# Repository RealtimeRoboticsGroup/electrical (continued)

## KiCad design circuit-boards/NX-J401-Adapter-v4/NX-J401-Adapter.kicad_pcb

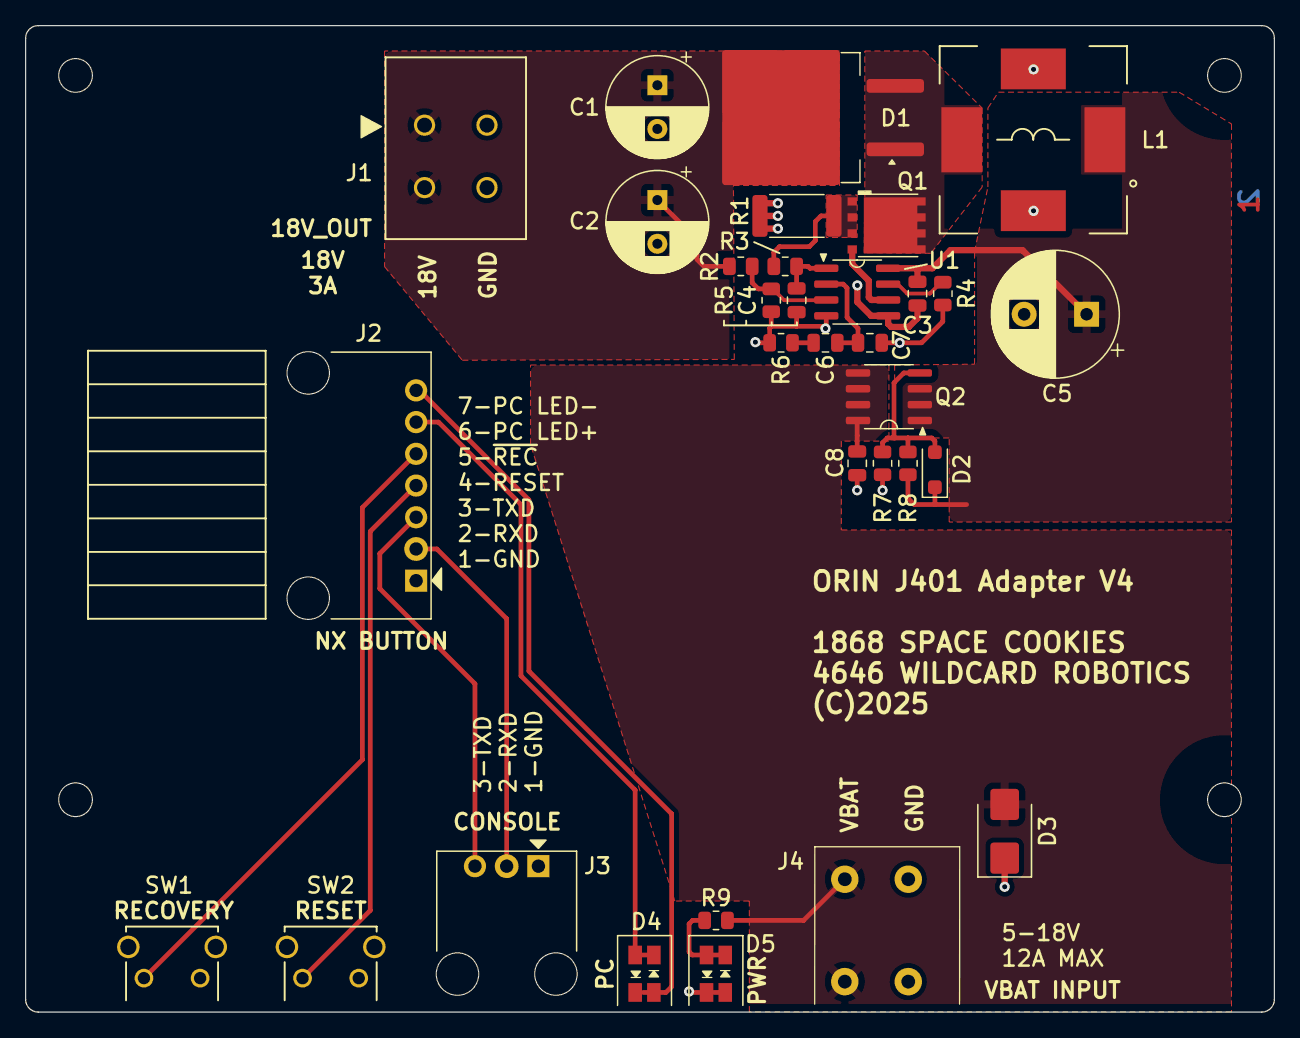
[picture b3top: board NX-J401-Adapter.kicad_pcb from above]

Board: 2 copper layers, 100.0 x 79.0 mm, 36 parts (0 on the bottom side), 21 nets.

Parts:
C1, C2: 82uF 35V; CP_Radial_D8.0mm_P3.50mm
C3, C6: 0.22uF-10%-50V-0805; C_0805_2012Metric
C4: 10pF-5%-50V-0805; C_0805_2012Metric
C5: 330uF 35V; CP_Radial_D10.0mm_P5.00mm
C7: 0.01uF-10%-50V-0805; C_0805_2012Metric
C8: 22uF-20%-25V-0805; C_0805_2012Metric
D1: STPS20M100SG-TR; TO-263-2
D2: 15V; D_SOD-123F
D3: 15V; D_SMB
D4: PC; LED-Dialight-5913001858F
D5: PWR; LED-Dialight-5913001858F
H1, H2, H3, H4: MountingHole; MountingHole_2.7mm_M2.5
J1: 18V_OUT; CONN_69140872_WRE
J2: NX BUTTON; 70555-0006
J3: CONSOLE; 70555-0002
J4: Power; Wurth-691406510002B
L1: 4.7 uH-8m-20%; INDUCTOR_IHLE-5050FH-Vishay
Q1: CSD16322Q5; TI-SON5x6
Q2: SI4483ADY-T1-GE3; SOIC-8_3.9x4.9mm_P1.27mm
R1: 4.0m-1%-2512; R_2512_6332Metric
R2: 14.0k-1%-0805; R_0805_2012Metric
R3: 100R-1%-0805; R_0805_2012Metric
R4: 59.0k-1%-0805; R_0805_2012Metric
R5, R6, R7: 1.05k-1%-0805; R_0805_2012Metric
R8: 20.0k-1%-0805; R_0805_2012Metric
R9: 4.99k-1%-0805; R_0805_2012Metric
SW1: RECOVERY; SW_TL1105VF100Q_EWI
SW2: RESET; SW_TL1105VF100Q_EWI
U1: LM3478MA; SOIC-8_3.9x4.9mm_P1.27mm

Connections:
/+18V_OUT: C1.1, C2.1, D1.2 (K), J1.1, R2.2
/Power Supply/Q_S: Q1.1 (S), Q1.2 (S), Q1.3 (S), R1.2, R3.1
/Power Supply/SW: D1.1 (A), D1.3 (A), L1.2, Q1.5 (D)
/Power Supply/V_IN: C3.1, C5.1, D2.1 (K), L1.1, Q2.1 (S), Q2.2 (S), Q2.3 (S), R8.2, U1.8 (V_{IN})
/RTN: J2.1, J3.1, SW1.2, SW2.2
/UART2_RXD: J2.2, J3.2
/UART2_TXD: J2.3, J3.3
/V_BAT: C8.1, D3.2 (A2), J4.1, Q2.5 (D), Q2.6 (D), Q2.7 (D), Q2.8 (D), R9.2
/~REC: J2.5, SW1.1
/~SYS_RESET: J2.4, SW2.1
GND: C1.2, C2.2, C3.2, C4.2, C5.2, C7.2, C8.2, D3.1 (A1), D5.2 (RedA), D5.4 (Green-K), J1.2, J4.2, L1.3, L1.4, R1.1, R4.1, R5.1, R6.1, R7.1, U1.4 (AGND), U1.5 (PGND)
unnamed: C6.2, R6.2
unnamed: D2.2 (A), Q2.4 (G), R7.2, R8.1
unnamed: D4.1 (Red-K), D4.3 (Green-A), J2.6
unnamed: D4.2 (RedA), D4.4 (Green-K), J2.7
unnamed: D5.1 (Red-K), D5.3 (Green-A), R9.1
unnamed: Q1.4 (G), U1.6 (DR)
unnamed: C6.1, C7.1, U1.2 (COMP)
unnamed: R4.2, U1.7 (FA/SD)
unnamed: R2.1, R5.2, U1.3 (FB)
unnamed: C4.1, R3.2, U1.1 (I_{SEN})

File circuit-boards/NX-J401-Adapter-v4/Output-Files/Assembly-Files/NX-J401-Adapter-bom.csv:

"Item","QUANTITY","Reference","Value","MFG","MFG P/N","DIST","DIST P/N"
"1","1","C4","10pF-5%-50V-0805","Samsung Electro-Mechanics","CL21C100CBANNNC","Digikey","1276-2561-1-ND"
"2","1","C5","330uF 35V","Rubycon","35PZJ330M10X9","Digikey","1189-35PZJ330M10X9-ND"
"3","1","C7","0.01uF-10%-50V-0805","Samsung Electro-Mechanics","CL21B103KBANNNC","Digikey","1276-1015-1-ND"
"4","1","C8","22uF-20%-25V-0805","Samsung Electro-Mechanics","CL21A226MAYNNNE","Digikey","1276-CL21A226MAYNNNECT-ND"
"5","2","C1,C2","82uF 35V","Panasonic Electronic Components","35SEPF82M","Digikey","P16345-ND"
"6","2","C3,C6","0.22uF-10%-50V-0805","KEMET","C0805C224K5RAC7800","Digikey","399-C0805C224K5RACTUCT-ND"
"7","1","D1","STPS20M100SG-TR","STmicroelectronics","STPS20M100SG-TR","Digikey","497-10993-1-ND"
"8","1","D2","15V","Nexperia","BZT52H-C15,115","Digikey","1727-3593-1-ND"
"9","1","D3","15V","Littelfuse","SZ1SMB15CAT3G","Digikey","F11544CT-ND"
"10","2","D4,D5","-- mixed values --","Dialight","5913001858F","Digikey","350-5913001858FCT-ND"
"11","1","J1","18V_OUT","Würth Elektronik","691408720002B","Digikey","732-691408720002B-ND"
"12","1","J2","NX BUTTON","Molex","0705550041","Digikey","WM4180-ND"
"13","1","J3","CONSOLE","Molex","0705550037","Digikey","WM4176-ND"
"14","1","J4","Power","Wurth","691406510002B","Digikey","732-691406510002B-ND"
"15","1","L1","4.7 uH-8m-20%","Vishay Dale","IHLE5050FHER4R7M5A ","Mouser","70-IHLE5050FHR4R7M5A "
"16","1","Q1","CSD16322Q5","Texas Instruments","CSD16322Q5","Digikey","296-25112-1-ND"
"17","1","Q2","SI4483ADY-T1-GE3","Vishay","SI4483ADY-T1-GE3","Digikey","SI4483ADY-T1-GE3CT-ND"
"18","1","R1","4.0m-1%-2512","Bourns Inc.","CRE2512-FZ-R004E-3","Digikey","CRE2512-FZ-R004E-3CT-ND"
"19","1","R2","14.0k-1%-0805","Yageo","RC0805FR-0714KL","Digikey","311-14.0KCRCT-ND"
"20","1","R3","100R-1%-0805","Yageo","RC0805FR-07100RL","Digikey","311-100CRCT-ND"
"21","1","R4","59.0k-1%-0805","Yageo","RC0805FR-0759KL","Digikey","311-59.0KCRCT-ND"
"22","1","R9","4.99k-1%-0805","Yageo","RC0805FR-07499RL","Digikey","311-499CRCT-ND"
"23","3","R5-R7","1.05k-1%-0805","Yageo","RC0805FR-071K05L","Digikey","311-1.05KCRCT-ND"
"24","2","SW1,SW2","-- mixed values --","E-Switch","TL1105VF100Q","Digikey","EG2507-ND"
"25","1","U1","LM3478MA","Texas Instruments","LM3478MAX/NOPB","Digikey","296-38111-1-ND"

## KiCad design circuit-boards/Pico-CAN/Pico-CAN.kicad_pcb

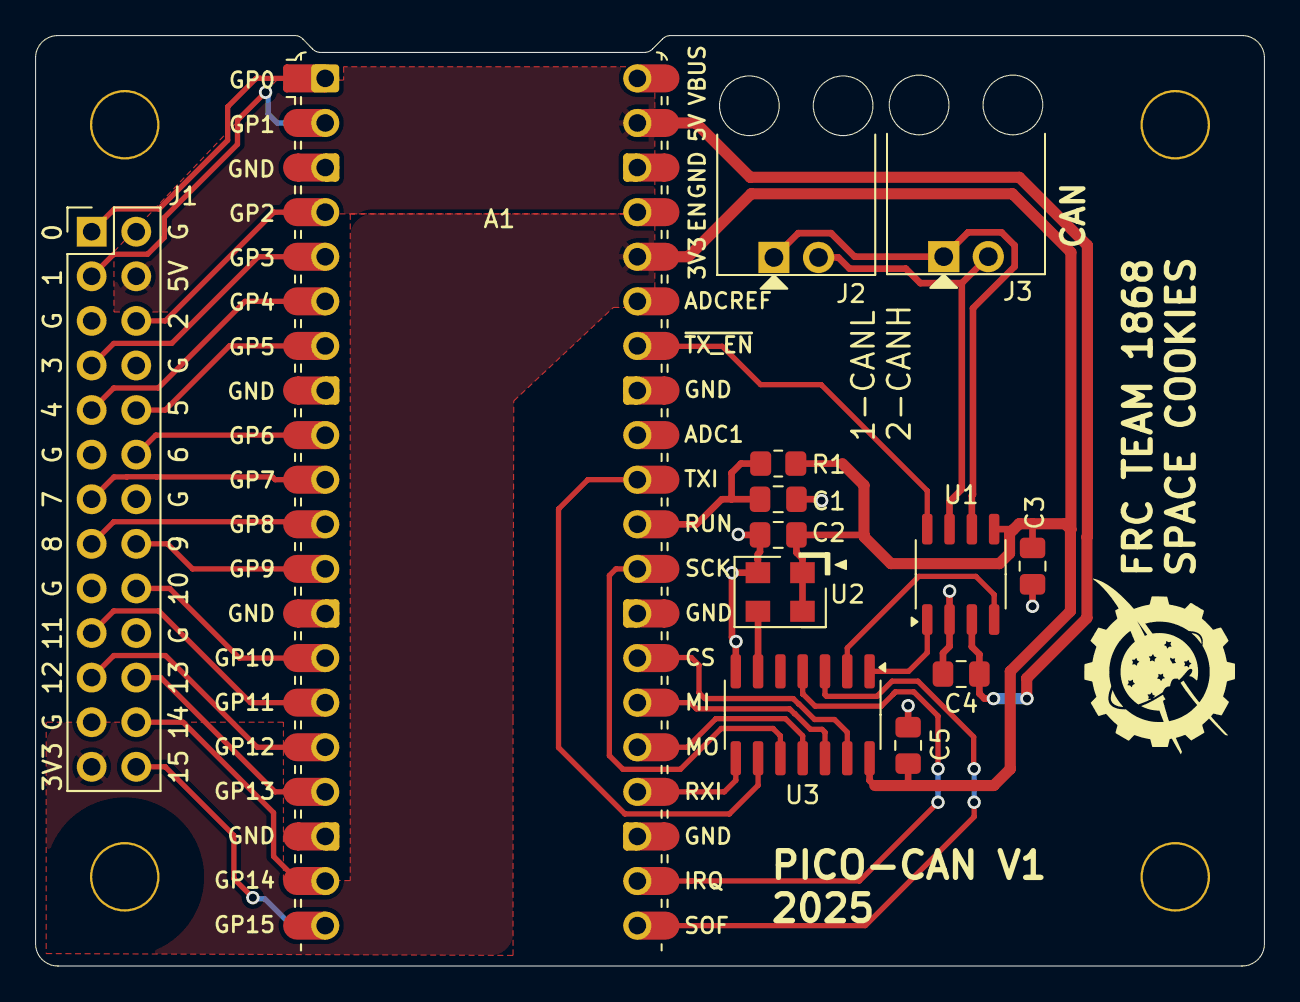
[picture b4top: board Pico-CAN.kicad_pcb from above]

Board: 2 copper layers, 70.0 x 53.0 mm, 17 parts (0 on the bottom side), 34 nets.

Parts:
A1: RaspberryPi_Pico2; RaspberryPi_Pico_Common_Unspecified
C1, C2, C3, C4, C5: 0.1uF-25V-10%-0805; C_0805_2012Metric_Pad1.18x1.45mm_HandSolder
H1, H2, H3, H4: MountingHole; MountingHole_3.7mm
J1: Expansion; PinHeader_2x13_P2.54mm_Vertical
J2, J3: CAN; 70555-0001
R1: 1.50k-1%-0805; R_0805_2012Metric_Pad1.20x1.40mm_HandSolder
U1: MCP2558FD; SO-8_3.9x4.9mm_P1.27mm
U2: 4.0 MHz; ECS-5032MV
U3: MCP2518FDT-H/SL; SO-14_3.9x8.65mm_P1.27mm

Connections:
+3V3: A1.36 (3V3), C2.1, C3.1, C5.1, J1.25, R1.1, U1.5 (V_{IO}), U2.1 (EN), U2.4 (+Vs), U3.14 (VDD)
+5V: A1.39 (VSYS), C4.1, J1.4, U1.3 (V_{DD})
/CANRX: U1.4 (RXD), U3.2 (RXCAN)
/CANTX: U1.1 (TXD), U3.1 (TXCAN)
/CAN_H: J2.2, J3.2, U1.7 (CANH)
/CAN_L: J2.1, J3.1, U1.6 (CANL)
/GPIO0: A1.1 (GPIO0), J1.1
/GPIO1: A1.2 (GPIO1), J1.3
/GPIO2: A1.4 (GPIO2), J1.6
/GPIO3: A1.5 (GPIO3), J1.7
/GPIO4: A1.6 (GPIO4), J1.9
/GPIO5: A1.7 (GPIO5), J1.10
/GPIO6: A1.9 (GPIO6), J1.12
/GPIO7: A1.10 (GPIO7), J1.13
/GPIO8: A1.11 (GPIO8), J1.15
/GPIO9: A1.12 (GPIO9), J1.16
/GPIO10: A1.14 (GPIO10), J1.18
/GPIO11: A1.15 (GPIO11), J1.19
/GPIO12: A1.16 (GPIO12), J1.21
/GPIO13: A1.17 (GPIO13), J1.22
/GPIO14: A1.19 (GPIO14), J1.24
/GPIO15: A1.20 (GPIO15), J1.26
/SPI0_MISO: A1.26 (SPI0_RX), U3.12 (SDO)
/SPI0_MOSI: A1.25 (SPI0_TX), U3.11 (SDI)
/SPI0_SCK: A1.29 (SPI0_SCK), U3.10 (SCK)
/START_OF_FRAME: A1.21 (GPIO16), U3.3 (SOF)
/XCVR_STBY: A1.34 (GPIO28), U1.8 (S)
/~CAN_IRQ: A1.22 (GPIO17), U3.4 (~INT)
/~CAN_RX_IRQ: A1.24 (GPIO18), U3.8 (~INT1)
/~CAN_TX_IRQ: A1.31 (GPIO26), U3.9 (~INT0)
/~SPI0_CS: A1.27 (~SPI0_CSn), U3.13 (~CS)
GND: A1.3 (GND), A1.8 (GND), A1.13 (GND), A1.18 (GND), A1.23 (GND), A1.28 (GND), A1.33 (AGND), A1.38 (GND), C1.2, C2.2, C3.2, C4.2, C5.2, J1.2, J1.5, J1.8, J1.11, J1.14, J1.17, J1.20, J1.23, U1.2 (V_{SS}), U2.2 (GND), U3.7 (VSS)
unnamed: A1.30 (RUN), C1.1, R1.2
unnamed: U2.3 (OUT), U3.6 (OSC1)

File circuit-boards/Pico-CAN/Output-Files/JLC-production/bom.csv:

Designator,Footprint,Quantity,Value,LCSC Part #
A1,RaspberryPi_Pico_Common_Unspecified,1,RaspberryPi_Pico2,
"C1, C2, C3, C4, C5",0805,5,0.1uF-25V-10%-0805,C519981
D1,SOT-23,1,PESD1CAN,C2984756
"J1, J2",70555-0001,2,CAN1,
J3,PinHeader_2x13_P2.54mm_Vertical,1,Expansion,
R1,0805,1,1.50k-1%-0805,C114555
U1,JLC-OSC-SMD3225-4P,1,4.0 MHz,C2901552
U2,SO-8_3.9x4.9mm_P1.27mm,1,MCP2558FD,C124015
U3,SO-14_3.9x8.65mm_P1.27mm,1,MCP2518FDT-H/SL,C626759

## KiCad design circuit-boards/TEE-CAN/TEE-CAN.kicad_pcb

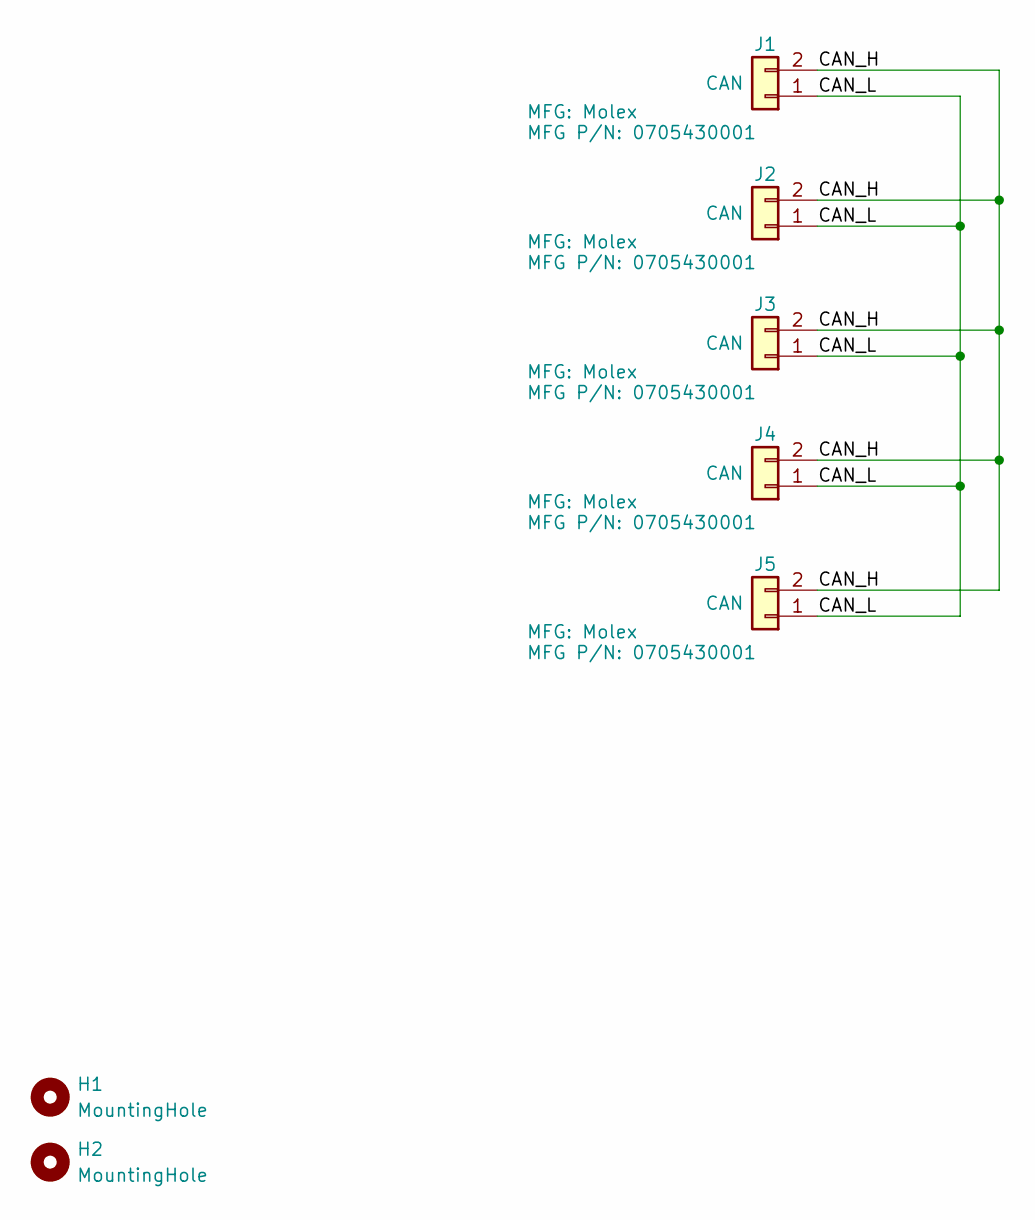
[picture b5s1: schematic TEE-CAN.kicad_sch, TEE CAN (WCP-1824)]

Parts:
H1, H2: MountingHole; MountingHole_3.2mm_M3
J1, J2, J3, J4, J5: CAN; 70543-0001; MFG P/N 0705430001

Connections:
/CAN_H: J1.2, J2.2, J3.2, J4.2, J5.2
/CAN_L: J1.1, J2.1, J3.1, J4.1, J5.1

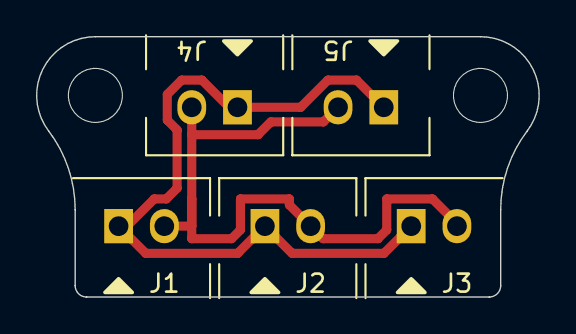
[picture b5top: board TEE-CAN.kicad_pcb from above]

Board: 2 copper layers, 27.9 x 14.5 mm, 7 parts (0 on the bottom side), 2 nets.

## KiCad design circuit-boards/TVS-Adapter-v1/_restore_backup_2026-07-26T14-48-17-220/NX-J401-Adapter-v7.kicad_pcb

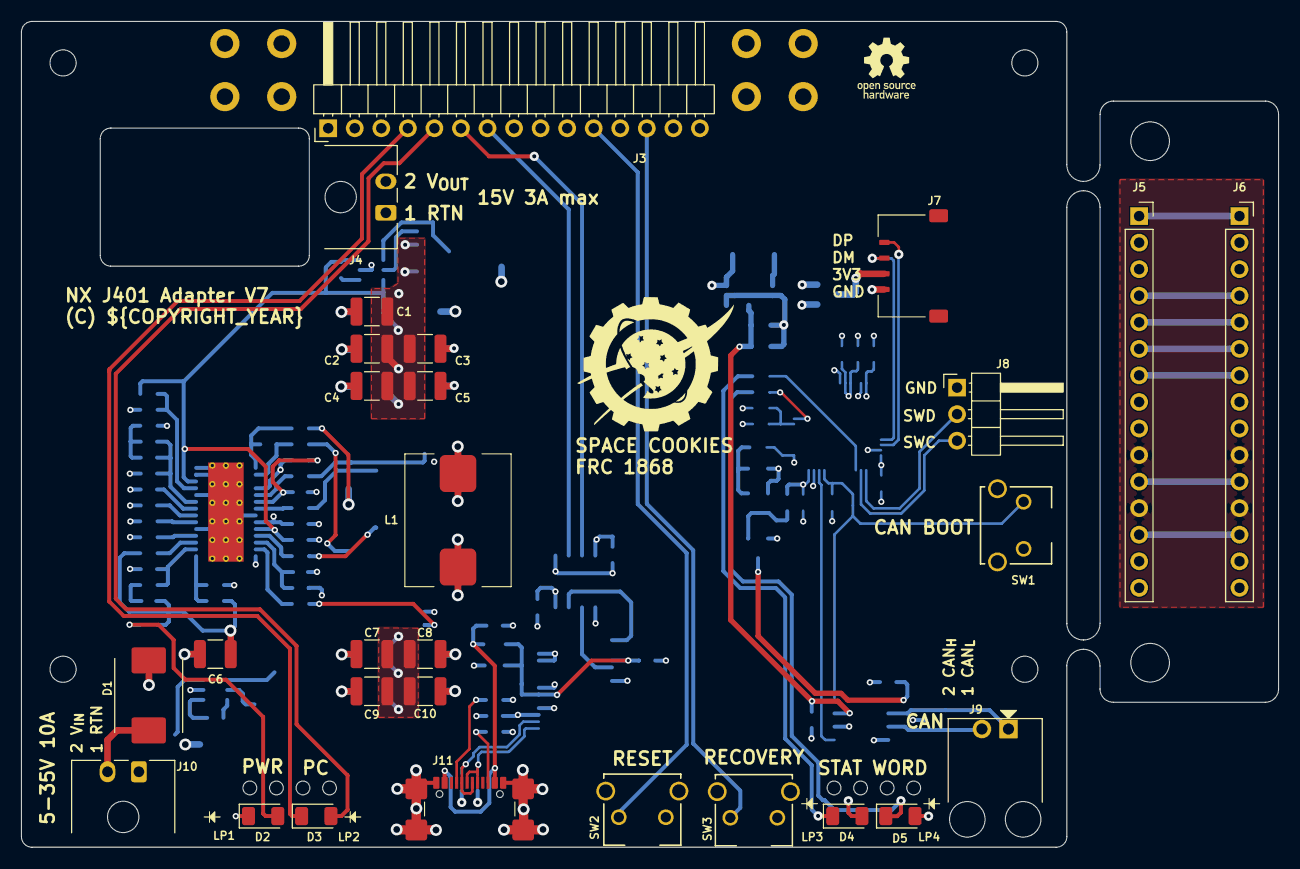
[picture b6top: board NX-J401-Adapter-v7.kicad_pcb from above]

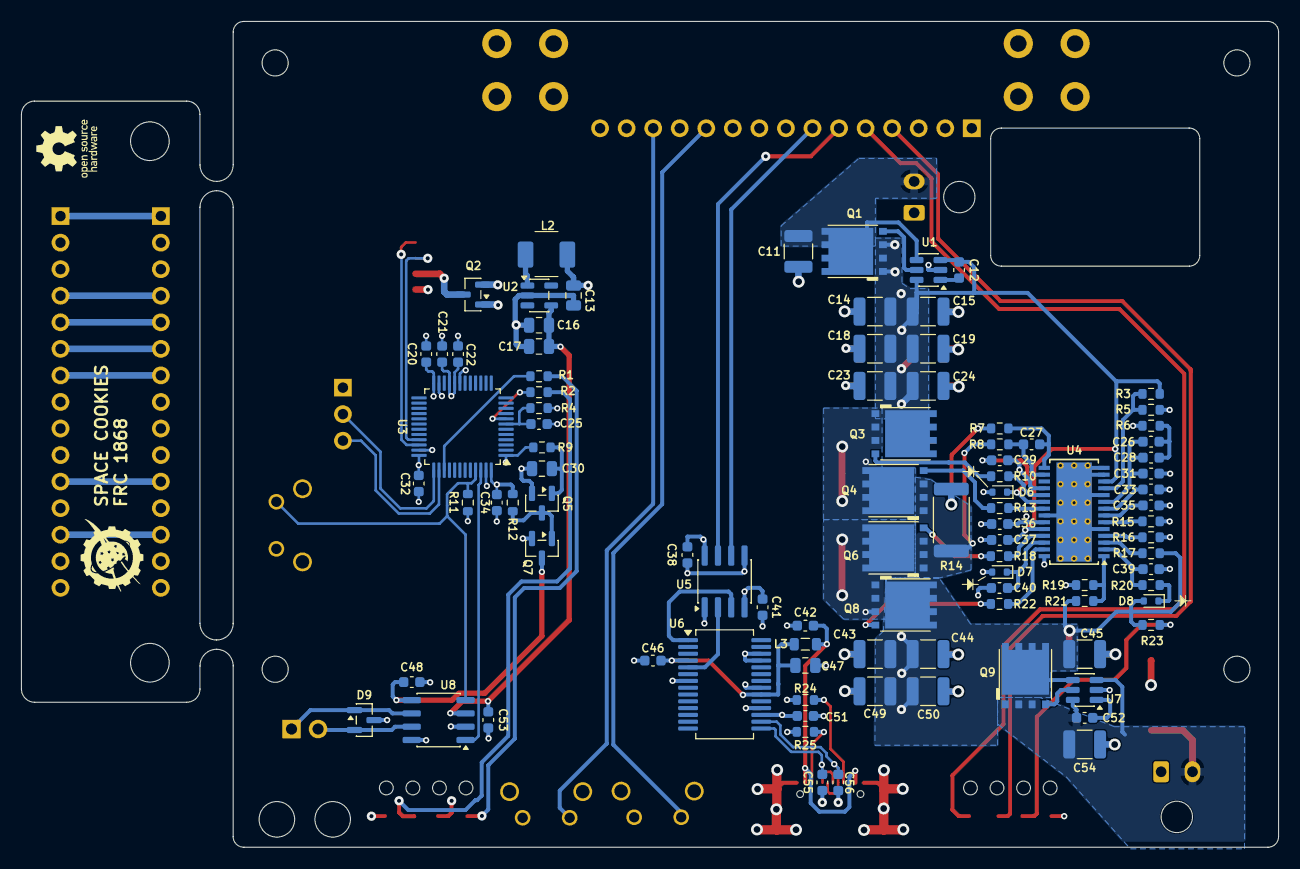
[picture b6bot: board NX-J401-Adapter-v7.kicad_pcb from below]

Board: 4 copper layers, 120.3 x 79.0 mm, 136 parts (95 on the bottom side), 84 nets.

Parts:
C1, C2, C3, C4, C5, C6, C7, C8, C9, C10, C11, C14, C15, C18, C19, C23, C24, C43, C44, C45, C49, C50, C54: 10uF-50V-10%-X7R-1210; C_1210_3225Metric
C12, C20, C21, C22, C25, C29, C32, C34, C37, C38, C39, C40, C41, C46, C48, C51, C52, C53: 0.1uF-50V-10%-0603; C_0603_1608Metric
C13, C16, C17, C30, C47: 22uF-10%-16V-0805; C_0805_2012Metric
C26, C28: 5.6nF-10%-50V-0603; C_0603_1608Metric
C27, C55, C56: 47pF-50V-10%-0603; C_0603_1608Metric
C31: 270pF-10%-50V-0603; C_0603_1608Metric
C33, C42: 15nF-10%-50V-0603; C_0603_1608Metric
C35: 150pF-50V-10%-0603; C_0603_1608Metric
C36: 1uF-50V-10%-0603; C_0603_1608Metric
D1: 24V; D_SMC_Littelfuse_DO-214AB
D2: PWR; LED_1206_3216Metric
D3: PC; LED_1206_3216Metric
D4: STAT; LED_1206_3216Metric
D5: WORD; LED_1206_3216Metric
D6, D7, D8: BAT54KFILM; D_SOD-523
D9: PESD1CAN; SOT-23
H1, H2, H5, H6: MountingHole; MountingHole_2.5mm
H3, H4: M3.7 MountingHole; MountingHole_3.7mm
J1, J2: Terminal; Keystone-7774
J3: NX CONTROL & UART; PinHeader_1x15_P2.54mm_Horizontal
J4: 15V; Molex_Micro-Fit_3.0_43650-0200_1x02_P3.00mm_Horizontal
J5, J6: NX CONTROL & UART; PinSocket_1x15_P2.54mm_Vertical
J7: USB1; Molex-PicoLatch-5040500491
J8: SWD; PinHeader_1x03_P2.54mm_Horizontal
J9: CAN1; Molex-70555-0001
J10: POWER; Molex_Micro-Fit_3.0_43650-0200_1x02_P3.00mm_Horizontal
J11: USB_C_Receptacle_USB2.0_14P; GCT-USB-C-USB4110-GF-A
L1: 2.2uH-19A-5.1mohm-20%; Koher-MDA1050
L2: 2.2uH-41mOhm-20%; KOHER-MDA4020-2R2M
L3: HZ0805E601R-10; L_0805_2012Metric
LOGO1: SPACE COOKIES LOGO; SPACE_COOKIES_LOGO_15mm
LOGO2: SPACE COOKIES LOGO; SPACE_COOKIES_LOGO_7mm
LP1, LP2, LP3, LP4: Bivar-SLP3-150-100-F
Q1, Q6, Q8, Q9: CSD19534Q5A; TI-SON5x6
Q2, Q7: SI2301CDS-T1-GE3; SOT-23
Q3, Q4: CSD17578Q5A; TI-SON5x6
Q5: SS8050; SOT-23
R1, R2: 1K-1%-0603; R_0603_1608Metric
R3: 357K-1%-0603; R_0603_1608Metric
R4, R11, R15: 13K-1%-0603; R_0603_1608Metric
R5: 20K-1%-0603; R_0603_1608Metric
R6: 5.9k-1%-0603; R_0603_1608Metric
R7, R8: 100R-1%-0603; R_0603_1608Metric
R9: 1M-1%-0603; R_0603_1608Metric
R10, R13, R18, R22: 0R-1%-0603; R_0603_1608Metric
R12, R19: 93.1k-1%-0603; R_0603_1608Metric
R14: 10mOhm-3W-1%-2512; R_2512_6332Metric
R16: 205K-1%-0603; R_0603_1608Metric
R17, R23: 2K-1%-0603; R_0603_1608Metric
R20: 10R0-1%-0603; R_0603_1608Metric
R21: 249K-1%-0603; R_0603_1608Metric
R24, R25: 5.1k-1%-0603; R_0603_1608Metric
SW1: CAN BOOT; SW_TL1105VF100Q_EWI
SW2: RESET; SW_TL1105VF100Q_EWI
SW3: RECOVERY; SW_TL1105VF100Q_EWI
U1, U7: LM74700QDBVRQ1; SOT-23-6
U2: TPS613222ADBV; SOT-23-5
U3: STM32G431CBTx; LQFP-48_7x7mm_P0.5mm
U4: HTSSOP-28-1EP_4.4x9.7mm_P0.65mm_EP3.4x9.5mm_ThermalVias
U5: ISO6721BDR; SOIC-8_3.9x4.9mm_P1.27mm
U6: FT232RNL; SSOP-28_5.3x10.2mm_P0.65mm
U8: TJA1051T/3/1J; SO-8_3.9x4.9mm_P1.27mm

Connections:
3V3_USB: C41.1, C51.1, U5.1 (VCC1), U6.17 (3V3OUT)
/3V3_BTN: C38.1, J3.1, U5.8 (VCC2)
/15V 3A Buck-Boost Power Supply/+V_OUT: C1.1, C2.1, C3.1, C4.1, C5.1, C12.1, C14.1, C15.1, C18.1, C19.1, C23.1, C24.1, C37.1, Q1.1 (S), Q1.2 (S), Q1.3 (S), Q3.5 (D), R3.1, U1.3 (EN), U1.6 (A), U4.12 (VOSNS), U4.24 (BIAS)
/15V 3A Buck-Boost Power Supply/HDRV1: Q8.4 (G), R22.2
/15V 3A Buck-Boost Power Supply/HDRV2: Q3.4 (G), R10.2
/15V 3A Buck-Boost Power Supply/LDRV1: Q6.4 (G), R18.2
/15V 3A Buck-Boost Power Supply/LDRV2: Q4.4 (G), R13.2
/15V 3A Buck-Boost Power Supply/RCS: Q4.1 (S), Q4.2 (S), Q4.3 (S), Q6.1 (S), Q6.2 (S), Q6.3 (S), R8.2, R14.1
/15V 3A Buck-Boost Power Supply/SW1: C40.2, L1.1, Q6.5 (D), Q8.1 (S), Q8.2 (S), Q8.3 (S), U4.28 (SW1)
/15V 3A Buck-Boost Power Supply/SW2: C29.2, L1.2, Q3.1 (S), Q3.2 (S), Q3.3 (S), Q4.5 (D), U4.18 (SW2)
/15V 3A Buck-Boost Power Supply/Vcc: C36.1, D6.2 (A), D7.2 (A), U4.23 (VCC)
/CANable2.0/3V3: C13.1, C20.1, C21.1, C22.1, C32.1, C34.1, D4.2 (A), D5.2 (A), L2.1, Q2.2 (S), Q7.2 (S), R4.1, R9.1, R12.1, SW1.1, U3.1 (VBAT), U3.20 (VREF+), U3.21 (VDDA), U3.24 (VDD), U3.36 (VDD), U3.48 (VDD)
/CANable2.0/3V3_CAN: C48.1, Q7.3 (D), U8.5 (VIO)
/CANable2.0/3V3_USB: J7.2, Q2.3 (D)
/CANable2.0/5V_CAN: C16.1, C17.1, C53.1, U2.4 (VOUT), U8.3 (VCC)
/CANable2.0/BOOT0: R11.1, SW1.2, U3.45 (FDCAN1_RX), U8.4 (RXD)
/CANable2.0/CAN_H: D9.2 (K1), J9.2, U8.7 (CANH)
/CANable2.0/CAN_L: D9.1 (K1), J9.1, U8.6 (CANL)
/CANable2.0/CAN_TX: U3.46 (FDCAN1_TX), U8.1 (TXD)
/CANable2.0/GND_CAN: C13.2, C16.2, C17.2, C20.2, C21.2, C22.2, C25.2, C30.2, C32.2, C34.2, C48.2, C53.2, D9.3 (KK), J7.1, J8.1, Q2.1 (G), Q5.2 (E), R11.2, U2.2 (GND), U3.19 (VSSA), U3.23 (VSS), U3.35 (VSS), U3.47 (VSS), U8.2 (GND), U8.8 (S)
/CANable2.0/NRST: C25.1, R4.2, U3.7 (PG10)
/CANable2.0/STAT_LED: R1.2, U3.39 (PA15)
/CANable2.0/SWCLK: J8.3, U3.38 (SYS_JTCK-SWCLK)
/CANable2.0/SWDIO: J8.2, U3.37 (SYS_JTMS-SWDIO)
/CANable2.0/USB_DM: J7.3, U3.33 (USB_DM)
/CANable2.0/USB_DP: J7.4, U3.34 (USB_DP)
/CANable2.0/WORD_LED: R2.2, U3.8 (PA0)
/NX-Button Interface/3V3_BTN: J5.1, J6.1
/NX-Button Interface/GND_BTN: J5.10, J5.12, J6.10, J6.12
/NX-Button Interface/NX_PC_LED+: J5.5, J6.5
/NX-Button Interface/NX_PC_LED-: J5.4, J6.4
/NX-Button Interface/UART2_RXD: J5.6, J6.6
/NX-Button Interface/UART2_TXD: J5.7, J6.7
/NX-Button Interface/~REC: J5.13, J6.13
/NX-Button Interface/~SYS_RESET: J5.11, J6.11
/NX_PC_LED+: D3.2 (A), J3.5
/NX_PC_LED-: D3.1 (K), J3.4
/UART2_RXD: J3.6, U5.7 (IN_{A})
/UART2_TXD: J3.7, U5.6 (OUT_{B})
/VIN_PS: C6.1, C7.1, C8.1, C9.1, C10.1, C43.1, C44.1, C45.1, C49.1, C50.1, D8.2 (A), Q8.5 (D), Q9.5 (D), R17.1, R21.1, R23.1, U7.4 (C)
/V_IN: C52.1, C54.1, D1.2 (A2), J10.2, Q9.1 (S), Q9.2 (S), Q9.3 (S), U7.3 (EN), U7.6 (A)
/V_OUT: C11.1, J4.2, Q1.5 (D), U1.4 (C)
/~REC: J3.13, SW3.1
/~SYS_RESET: J3.11, SW2.1
GND: C1.2, C2.2, C3.2, C4.2, C5.2, C6.2, C7.2, C8.2, C9.2, C10.2, C11.2, C14.2, C15.2, C18.2, C19.2, C23.2, C24.2, C31.2, C33.2, C35.2, C36.2, C37.2, C39.2, C43.2, C44.2, C45.2, C49.2, C50.2, C54.2, D1.1 (A1), D2.1 (K), J4.1, J10.1, R5.2, R6.2, R7.1, R14.2, R15.2, R16.2, R19.2, U1.2 (GND), U4.5 (DITH), U4.10 (AGND), U4.13 (ISNS(-)), U4.14 (ISNS(+)), U4.22 (PGND), U4.EP (PGND), U7.2 (GND)
GND1: C38.2, J3.10, J3.12, SW2.2, SW3.2, U5.5 (GND2)
GND_USB: C41.2, C42.2, C46.2, C47.2, C51.2, C55.2, C56.2, J11.A1B12 (GND), J11.B1A12 (GND), J11.S1 (SHIELD), R24.2, R25.2, U5.4 (GND1), U6.7 (GND), U6.18 (GND), U6.21 (GND), U6.25 (AGND), U6.26 (TEST)
unnamed: C26.2, C28.2, R6.1
unnamed: C42.1, J11.A4B9 (VBUS), J11.B4A9 (VBUS), L3.1
unnamed: D2.2 (A), R23.2
unnamed: D4.1 (K), R1.1
unnamed: D5.1 (K), R2.1
unnamed: C29.1, D6.1 (K), U4.20 (BOOT2)
unnamed: C40.1, D7.1 (K), U4.26 (BOOT1)
unnamed: D8.1 (K), R20.1
unnamed: J11.A5 (CC1), R24.1
unnamed: J11.B5 (CC2), R25.1
unnamed: Q1.4 (G), U1.5 (G)
unnamed: C30.1, Q5.1 (B), R9.2
unnamed: Q5.3 (C), Q7.1 (G), R12.2
unnamed: Q9.4 (G), U7.5 (G)
unnamed: C12.2, U1.1 (VCAP)
unnamed: L2.2, U2.1 (SW)
unnamed: C26.1, C28.1, C31.1, U4.9 (COMP)
unnamed: C27.1, R8.1, U4.16 (CS)
unnamed: C27.2, R7.2, U4.15 (CSG)
unnamed: R19.1, R21.2, U4.1 (EN/UVLO)
unnamed: R3.2, R5.1, U4.11 (FB)
unnamed: R22.1, U4.27 (HDRV1)
unnamed: R10.1, U4.19 (HDRV2)
unnamed: R18.1, U4.25 (LDRV1)
unnamed: R13.1, U4.21 (LDRV2)
unnamed: R16.1, U4.4 (MODE)
unnamed: R15.1, U4.6 (RT)
unnamed: C35.1, U4.7 (SLOPE)
unnamed: C33.1, U4.8 (SS)
unnamed: C39.1, R20.2, U4.2 (VIN)
unnamed: R17.2, U4.3 (VISNS)
unnamed: U5.3 (IN_{B}), U6.1 (TXD)
unnamed: U5.2 (OUT_{A}), U6.5 (RXD)
unnamed: C55.1, J11.A6 (D+), J11.B6 (D+), U6.15 (USBD+)
unnamed: C56.1, J11.A7 (D-), J11.B7 (D-), U6.16 (USBD-)
unnamed: C46.1, C47.1, L3.2, U6.4 (VCCIO), U6.20 (VCC)
unnamed: C52.2, U7.1 (VCAP)
